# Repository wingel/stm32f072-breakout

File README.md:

STM32F072 Breakout Board
========================

This is a small breakout board for the STM32F072 MCU in a LQFP48
package.  I wanted something that would make it easier to try things
out with a small STM2F07 MCU and this PCB is the result.  This PCB
should also work with the STM32F042 MCU and maybe even other STM MCUs
in the same package, but I have not tested that.

Features
--------

* A Micro USB for powering the board and communicating with a host

* All other I/O pins are routed to a 2.54mm pin header

* A voltage regulator which provides VDD

* VIO and VDDA are normally provided from VDD via 0Ω resistors, but
  can optionally be provided externally via a pin header

* RESET and BOOT buttons

* A power LED which shows when the PCB is powered

* A user programmable LED which is connected to I/O pin PA10 (optional)

* PCB is 2 layers and smaller than 50x50mm and so ordering from China
  will only cost about $10 + shipping for 10 PCBs.

Firmware
========

A firmware based on [ChibiOS-RT](http://www.chibios.org/) can be found
on [GitHub](https://github.com/wingel/chibios-stm).

License
=======

[stm32f072-breakout](https://github.com/wingel/stm32f072-breakout) by
[Christer Weinigel](mailto:christer@weinigel.se) is licensed under a
[Creative Commons Attribution 4.0 International
License](http://creativecommons.org/licenses/by/4.0/).

The intent is to make this PCB available to anyone that finds it
useful as long as I get credit for the original design.  If you want
to use the design and have issues with the above license, please
contact me.

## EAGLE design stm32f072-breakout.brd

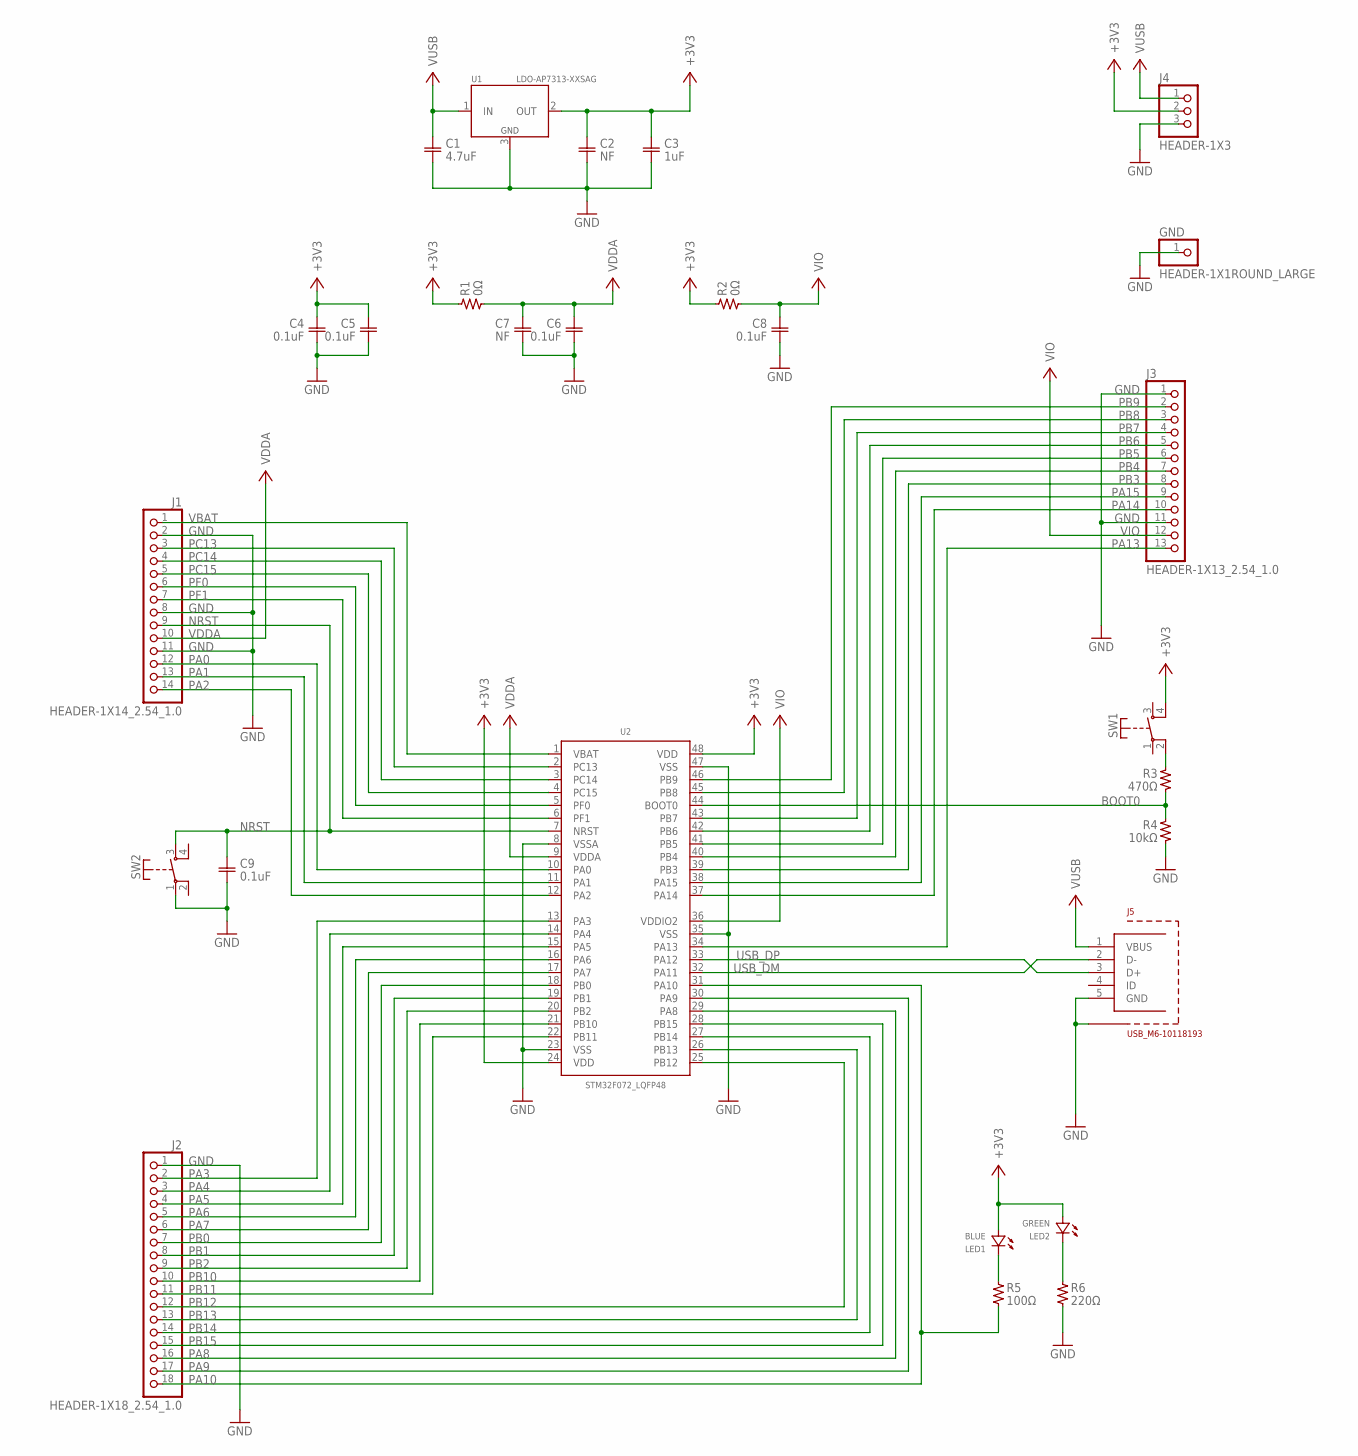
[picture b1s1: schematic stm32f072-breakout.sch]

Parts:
C1: 4.7uF; 0603
C2, C7: NF; 0603
C3: 1uF; 0603
C4, C5, C6, C8, C9: 0.1uF; 0603
GND: HEADER-1X1ROUND_LARGE; 1X01_ROUND_LARGE
J1: HEADER-1X14_2.54_1.0; 1X14_OVAL
J2: HEADER-1X18_2.54_1.0; 1X18_OVAL
J3: HEADER-1X13_2.54_1.0; 1X13_OVAL
J4: HEADER-1X3; 1X03_OVAL
J5: USB_M6-10118193; FCI-10118193
LED1: BLUE; 0603-POL
LED2: GREEN; 0603-POL
R1, R2: 0Ω; 0603
R3: 470Ω; 0603
R4: 10kΩ; 0603
R5: 100Ω; 0603
R6: 220Ω; 0603
SW1, SW2: SWITCH_OFF(ON)_2-MJTP1140A; MJTP1140A
U1: LDO-AP7313-XXSAG; SOT23
U2: STM32F072_LQFP48; LQFP48

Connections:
+3V3: C2.1, C3.1, C4.1, C5.1, J4.2, LED1.2 (A), LED2.2 (A), R1.1, R2.1, SW1.4, U1.2 (OUT), U2.24 (VDD), U2.48 (VDD)
BOOT0: R3.2, R4.1, U2.44 (BOOT0)
GND: C1.2, C2.2, C3.2, C4.2, C5.2, C6.2, C7.2, C8.2, C9.2, GND.1, J1.2, J1.8, J1.11, J2.1, J3.1, J3.11, J4.3, J5.5 (GND), J5.SHIELD@1 (SHIELD), J5.SHIELD@2 (SHIELD), J5.SHIELD@3 (SHIELD), J5.SHIELD@4 (SHIELD), J5.SHIELD@5 (SHIELD), J5.SHIELD@6 (SHIELD), J5.SHIELD@7 (SHIELD), J5.SHIELD@8 (SHIELD), R4.2, R6.2, SW2.1, U1.3 (GND), U2.8 (VSSA), U2.23 (VSS), U2.35 (VSS), U2.47 (VSS)
unnamed: R3.1, SW1.2
unnamed: LED1.1 (C), R5.1
unnamed: LED2.1 (C), R6.1
NRST: C9.1, J1.9, SW2.3, U2.7 (NRST)
PA0: J1.12, U2.10 (PA0)
PA1: J1.13, U2.11 (PA1)
PA2: J1.14, U2.12 (PA2)
PA3: J2.2, U2.13 (PA3)
PA4: J2.3, U2.14 (PA4)
PA5: J2.4, U2.15 (PA5)
PA6: J2.5, U2.16 (PA6)
PA7: J2.6, U2.17 (PA7)
PA8: J2.16, U2.29 (PA8)
PA9: J2.17, U2.30 (PA9)
PA10: J2.18, R5.2, U2.31 (PA10)
PA13: J3.13, U2.34 (PA13)
PA14: J3.10, U2.37 (PA14)
PA15: J3.9, U2.38 (PA15)
PB0: J2.7, U2.18 (PB0)
PB1: J2.8, U2.19 (PB1)
PB2: J2.9, U2.20 (PB2)
PB3: J3.8, U2.39 (PB3)
PB4: J3.7, U2.40 (PB4)
PB5: J3.6, U2.41 (PB5)
PB6: J3.5, U2.42 (PB6)
PB7: J3.4, U2.43 (PB7)
PB8: J3.3, U2.45 (PB8)
PB9: J3.2, U2.46 (PB9)
PB10: J2.10, U2.21 (PB10)
PB11: J2.11, U2.22 (PB11)
PB12: J2.12, U2.25 (PB12)
PB13: J2.13, U2.26 (PB13)
PB14: J2.14, U2.27 (PB14)
PB15: J2.15, U2.28 (PB15)
PC13: J1.3, U2.2 (PC13)
PC14: J1.4, U2.3 (PC14)
PC15: J1.5, U2.4 (PC15)
PF0: J1.6, U2.5 (PF0)
PF1: J1.7, U2.6 (PF1)
USB_DM: J5.2 (D-), U2.32 (PA11)
USB_DP: J5.3 (D+), U2.33 (PA12)
VBAT: J1.1, U2.1 (VBAT)
VDDA: C6.1, C7.1, J1.10, R1.2, U2.9 (VDDA)
VIO: C8.1, J3.12, R2.2, U2.36 (VDDIO2)
VUSB: C1.1, J4.1, J5.1 (VBUS), U1.1 (IN)

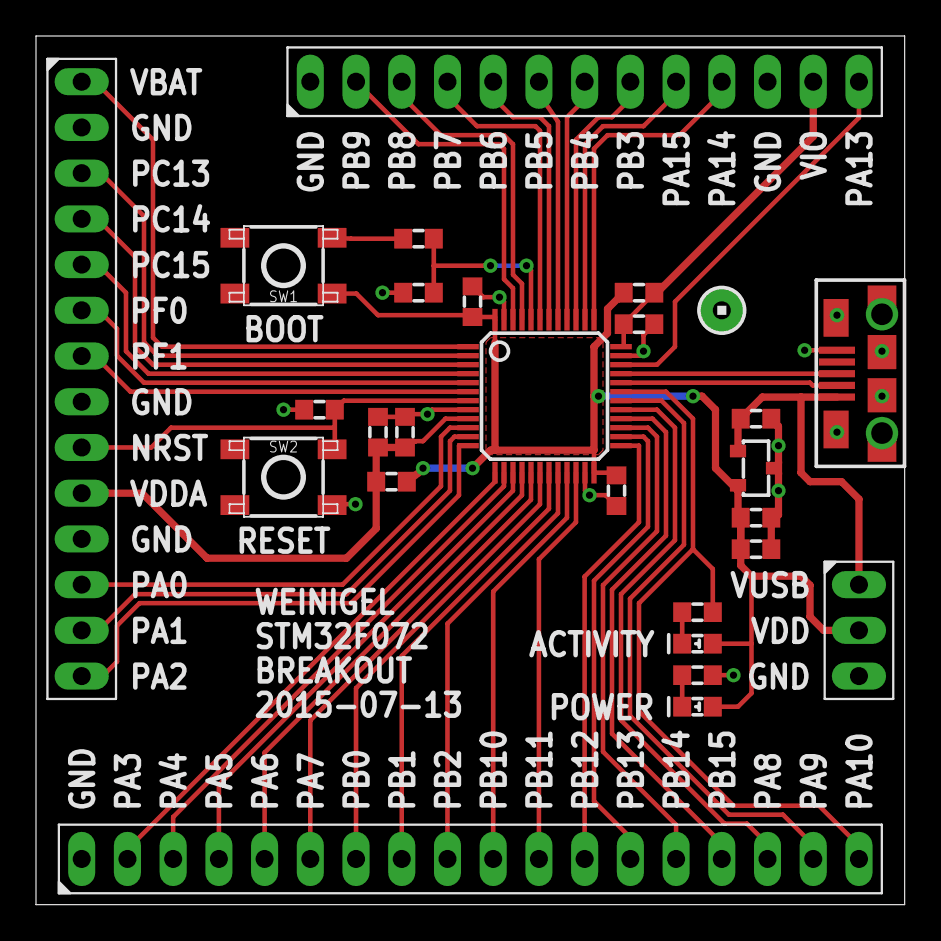
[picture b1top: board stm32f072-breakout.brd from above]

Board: 2 copper layers, 48.3 x 48.3 mm, 27 parts (0 on the bottom side), 48 nets.

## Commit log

2015-08-24 Create repository
2015-08-24 Add README
